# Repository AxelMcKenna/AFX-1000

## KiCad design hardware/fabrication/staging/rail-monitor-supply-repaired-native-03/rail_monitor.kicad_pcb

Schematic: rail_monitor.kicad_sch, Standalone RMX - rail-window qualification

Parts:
C1, C2, C3, C4, C5, C6, C7, C8, C9, C10, C11, C12, C13, C14, C15, C16, C17, C18, C19, C20, C21, C22, C23, C24, C25, C26, C27, C28, C29, C30, C31, C32, C33, C34, C35, C36: 100pF C0G 5%; C_0805_2012Metric
C37, C38, C39, C40, C41, C42, C43, C44, C45, C46, C47, C48: 100nF 16V X7R; C_0805_2012Metric
C49: 2.2uF 16V X7R; C_0805_2012Metric
C50: 10uF 16V X7R; C_0805_2012Metric
C51: 1uF 16V X7R; C_0805_2012Metric
J1, J3: Conn_01x03; PinHeader_1x03_P2.54mm_Vertical
J2: Conn_01x06; PinHeader_1x06_P2.54mm_Vertical
J4: Conn_01x02; PinHeader_1x02_P2.54mm_Vertical
R1, R7, R25, R31: 91k 0.01% 5ppm; R_0805_2012Metric
R2, R4, R8, R10, R11, R14, R16, R19, R21, R22, R26, R28, R32, R33, R35, R36, R39, R41, R44, R45, R47, R48, R51, R53, R56, R58, R59, R62, R64, R67, R69, R70, R73, R75, R77, R80, R82, R84, R85, R88, R90, R92, R96, R98, R99, R103, R105, R106, R108, R111: 10k 0.01% 5ppm; R_0805_2012Metric
R3: 3.57k 0.01% 5ppm; R_0805_2012Metric
R5, R12, R17, R23, R29, R37, R42, R49, R54, R60, R65, R71, R78, R86, R93, R100: 20M 1%; R_0805_2012Metric
R6, R13, R18, R24, R30, R38, R43, R50, R55, R61, R66, R72, R79, R87, R94, R101, R113: 10k 1%; R_0805_2012Metric
R9: 3.01k 0.01% 5ppm; R_0805_2012Metric
R15: 3.4k 0.01% 5ppm; R_0805_2012Metric
R20: 2.87k 0.01% 5ppm; R_0805_2012Metric
R27, R95: 11.5k 0.01% 5ppm; R_0805_2012Metric
R34: 604 0.01% 5ppm; R_0805_2012Metric
R40: 11.3k 0.01% 5ppm; R_0805_2012Metric
R46: 412 0.01% 5ppm; R_0805_2012Metric
R52, R63: 8.2k 0.01% 5ppm; R_0805_2012Metric
R57, R68: 1.78k 0.01% 5ppm; R_0805_2012Metric
R74, R81, R89: 499 0.01% 5ppm; R_0805_2012Metric
R76: 374 0.01% 5ppm; R_0805_2012Metric
R83: 127 0.01% 5ppm; Bourns_CRT0805
R91: 768 0.01% 5ppm; R_0805_2012Metric
R97: 270 0.01% 5ppm; R_0805_2012Metric
R102, R104: 100k 0.01% 5ppm; R_0805_2012Metric
R107, R109: 80.6k 0.01% 5ppm; R_0805_2012Metric
R110: 105k 0.01% 5ppm; R_0805_2012Metric
R112: 100k 1%; R_0805_2012Metric
R114: 330k 1%; R_0805_2012Metric
U1, U2, U3, U4: TLV1824IDR; SOIC-14_3.9x8.7mm_P1.27mm
U5: OPA4192ID; SOIC-14_3.9x8.7mm_P1.27mm
U6: REF5025EIDR; SOIC-8_3.9x4.9mm_P1.27mm
U7: TPS3808G01DBVR; SOT-23-6
U8: TPS3808G33DBVR; SOT-23-6
U9, U10, U11, U12: SN74LVC08APWR; TSSOP-14_4.4x5mm_P0.65mm

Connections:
/5V_DIG: J1.1, R88.1, R95.1
/5V_DIG_OV_OK: R100.1, R101.2, U4.13 (4_OUT), U10.13 (B)
/5V_DIG_OV_REF: C32.1, R99.2, R100.2, U4.11 (4+)
/5V_DIG_OV_REF_BASE: R97.2, R98.1, R99.1
/5V_DIG_OV_SENSE: C31.1, R95.2, R96.1, U4.10 (4-)
/5V_DIG_UV_OK: R93.1, R94.2, U4.14 (3_OUT), U10.12 (A)
/5V_DIG_UV_REF: C30.1, R91.2, R92.1, U4.8 (3-)
/5V_DIG_UV_RT_MID: R88.2, R89.1
/5V_DIG_UV_SENSE: C29.1, R89.2, R90.1, R93.2, U4.9 (3+)
/5V_DIG_WINDOW_OK: U10.11 (Y), U11.13 (B)
/AGND: C1.2, C2.2, C3.2, C4.2, C5.2, C6.2, C7.2, C8.2, C9.2, C10.2, C11.2, C12.2, C13.2, C14.2, C15.2, C16.2, C17.2, C18.2, C19.2, C20.2, C21.2, C22.2, C23.2, C24.2, C25.2, C26.2, C27.2, C28.2, C29.2, C30.2, C31.2, C32.2, C37.2, C38.2, C39.2, C40.2, C41.2, C42.2, C43.2, C44.2, C45.2, C46.2, C47.2, C48.2, C49.2, C50.2, C51.2, J1.3, J2.2, J3.1, J4.1, R2.2, R4.2, R8.2, R10.2, R16.2, R21.2, R26.2, R28.2, R32.2, R35.2, R41.2, R47.2, R53.2, R58.2, R64.2, R69.2, R75.2, R77.2, R82.2, R84.2, R90.2, R92.2, R96.2, R98.2, R111.2, R114.2, U1.12 (V-), U2.12 (V-), U3.12 (V-), U4.12 (V-), U5.3 (N19+), U5.5 (N12+), U5.10 (NBIAS_L+), U5.11 (V-), U5.12 (NBIAS_R+), U6.4 (GND), U7.2 (GND), U8.2 (GND), U9.7 (GND), U10.7 (GND), U11.7 (GND), U12.7 (GND)
/ANALOG_WINDOWS_OK: U12.3 (Y), U12.9 (A)
/BIAS_OK: U11.8 (Y), U12.4 (A)
/FIVES_OK: U11.11 (Y), U12.5 (B)
/HV_OK: U11.3 (Y), U12.1 (A)
/LOCAL_RAIL_OK: R113.2, U7.1 (RESET_N), U8.1 (RESET_N), U12.13 (B)
/LOWV_WINDOWS_OK: U12.6 (Y), U12.10 (B)
/LV_OK: U11.6 (Y), U12.2 (B)
/N12: J2.5, R104.1
/N12_FB: C34.2, R104.2, R105.2, U5.6 (N12-)
/N12_INV: C34.1, R39.1, R44.1, R105.1, U5.7 (N12_OUT)
/N12_OV_OK: R49.1, R50.2, U2.13 (4_OUT), U9.13 (B)
/N12_OV_REF: C16.1, R48.2, R49.2, U2.11 (4+)
/N12_OV_REF_BASE: R46.2, R47.1, R48.1
/N12_OV_REF_MID: R45.2, R46.1
/N12_OV_SENSE: C15.1, R44.2, U2.10 (4-)
/N12_UV_OK: R42.1, R43.2, U2.14 (3_OUT), U9.12 (A)
/N12_UV_REF: C14.1, R40.2, R41.1, U2.8 (3-)
/N12_UV_SENSE: C13.1, R39.2, R42.2, U2.9 (3+)
/N12_WINDOW_OK: U9.11 (Y), U11.5 (B)
/N19: J2.3, R102.1
/N19_FB: C33.2, R102.2, R103.2, U5.2 (N19-)
/N19_INV: C33.1, R14.1, R19.1, R103.1, U5.1 (N19_OUT)
/N19_OV_OK: R23.1, R24.2, U1.13 (4_OUT), U9.5 (B)
/N19_OV_REF: C8.1, R22.2, R23.2, U1.11 (4+)
/N19_OV_REF_BASE: R20.2, R21.1, R22.1
/N19_OV_SENSE: C7.1, R19.2, U1.10 (4-)
/N19_UV_OK: R17.1, R18.2, U1.14 (3_OUT), U9.4 (A)
/N19_UV_REF: C6.1, R15.2, R16.1, U1.8 (3-)
/N19_UV_SENSE: C5.1, R14.2, R17.2, U1.9 (3+)
/N19_WINDOW_OK: U9.6 (Y), U11.2 (B)
/NBIAS_L: J3.2, R106.1
/NBIAS_L_FB: C35.2, R106.2, R107.2, U5.9 (NBIAS_L-)
/NBIAS_L_INV: C35.1, R51.1, R56.1, R107.1, U5.8 (NBIAS_L_OUT)
/NBIAS_L_OV_OK: R60.1, R61.2, U3.1 (2_OUT), U10.2 (B)
/NBIAS_L_OV_REF: C20.1, R59.2, R60.2, U3.7 (2+)
/NBIAS_L_OV_REF_BASE: R57.2, R58.1, R59.1
/NBIAS_L_OV_SENSE: C19.1, R56.2, U3.6 (2-)
/NBIAS_L_UV_OK: R54.1, R55.2, U3.2 (1_OUT), U10.1 (A)
/NBIAS_L_UV_REF: C18.1, R52.2, R53.1, U3.4 (1-)
/NBIAS_L_UV_SENSE: C17.1, R51.2, R54.2, U3.5 (1+)
/NBIAS_L_WINDOW_OK: U10.3 (Y), U11.9 (A)
/NBIAS_R: J3.3, R108.1
/NBIAS_R_FB: C36.2, R108.2, R109.2, U5.13 (NBIAS_R-)
/NBIAS_R_INV: C36.1, R62.1, R67.1, R109.1, U5.14 (NBIAS_R_OUT)
/NBIAS_R_OV_OK: R71.1, R72.2, U3.13 (4_OUT), U10.5 (B)
/NBIAS_R_OV_REF: C24.1, R70.2, R71.2, U3.11 (4+)
/NBIAS_R_OV_REF_BASE: R68.2, R69.1, R70.1
/NBIAS_R_OV_SENSE: C23.1, R67.2, U3.10 (4-)
/NBIAS_R_UV_OK: R65.1, R66.2, U3.14 (3_OUT), U10.4 (A)
/NBIAS_R_UV_REF: C22.1, R63.2, R64.1, U3.8 (3-)
/NBIAS_R_UV_SENSE: C21.1, R62.2, R65.2, U3.9 (3+)
/NBIAS_R_WINDOW_OK: U10.6 (Y), U11.10 (B)
/P12: J2.4, R25.1, R31.1
/P12_OV_OK: R37.1, R38.2, U2.1 (2_OUT), U9.10 (B)
/P12_OV_REF: C12.1, R36.2, R37.2, U2.7 (2+)
/P12_OV_REF_BASE: R34.2, R35.1, R36.1
/P12_OV_REF_MID: R33.2, R34.1
/P12_OV_SENSE: C11.1, R31.2, R32.1, U2.6 (2-)
/P12_UV_OK: R29.1, R30.2, U2.2 (1_OUT), U9.9 (A)
/P12_UV_REF: C10.1, R27.2, R28.1, U2.4 (1-)
/P12_UV_SENSE: C9.1, R25.2, R26.1, R29.2, U2.5 (1+)
/P12_WINDOW_OK: U9.8 (Y), U11.4 (A)
/P19: J2.1, R1.1, R7.1
/P19_OV_OK: R12.1, R13.2, U1.1 (2_OUT), U9.2 (B)
/P19_OV_REF: C4.1, R11.2, R12.2, U1.7 (2+)
/P19_OV_REF_BASE: R9.2, R10.1, R11.1
/P19_OV_SENSE: C3.1, R7.2, R8.1, U1.6 (2-)
/P19_UV_OK: R5.1, R6.2, U1.2 (1_OUT), U9.1 (A)
/P19_UV_REF: C2.1, R3.2, R4.1, U1.4 (1-)
/P19_UV_SENSE: C1.1, R1.2, R2.1, R5.2, U1.5 (1+)
/P19_WINDOW_OK: U9.3 (Y), U11.1 (A)
/PRE_ANALOG_OK: J4.2, R114.1, U12.11 (Y)
/REF_2V5: C49.1, R3.1, R9.1, R15.1, R20.1, R27.1, R33.1, R40.1, R45.1, R52.1, R57.1, R63.1, R68.1, R76.1, R83.1, R91.1, R97.1, U6.6 (VOUT)
/STARTUP_CT: R112.2, U7.4 (CT)
/V3V3_IO: C43.1, C44.1, C45.1, C46.1, C47.1, C48.1, C51.1, J1.2, R6.1, R13.1, R18.1, R24.1, R30.1, R38.1, R43.1, R50.1, R55.1, R61.1, R66.1, R72.1, R79.1, R87.1, R94.1, R101.1, R112.1, R113.1, U7.3 (MR_N), U7.6 (VDD), U8.3 (MR_N), U8.5 (SENSE), U8.6 (VDD), U9.14 (VCC), U10.14 (VCC), U11.14 (VCC), U12.14 (VCC)
/V5_COARSE_SENSE: R110.2, R111.1, U7.5 (SENSE)
/V5_REG: C37.1, C38.1, C39.1, C40.1, C41.1, C42.1, C50.1, J2.6, R73.1, R80.1, R110.1, U1.3 (V+), U2.3 (V+), U3.3 (V+), U4.3 (V+), U5.4 (V+), U6.1 (EN), U6.2 (VIN)
/V5_REG_OV_OK: R86.1, R87.2, U4.1 (2_OUT), U10.10 (B)
/V5_REG_OV_REF: C28.1, R85.2, R86.2, U4.7 (2+)
/V5_REG_OV_REF_BASE: R83.2, R84.1, R85.1
/V5_REG_OV_RT_MID: R80.2, R81.1
/V5_REG_OV_SENSE: C27.1, R81.2, R82.1, U4.6 (2-)
/V5_REG_UV_OK: R78.1, R79.2, U4.2 (1_OUT), U10.9 (A)
/V5_REG_UV_REF: C26.1, R76.2, R77.1, U4.4 (1-)
/V5_REG_UV_RT_MID: R73.2, R74.1
/V5_REG_UV_SENSE: C25.1, R74.2, R75.1, R78.2, U4.5 (1+)
/V5_REG_WINDOW_OK: U10.8 (Y), U11.12 (A)
/WINDOWS_OK: U12.8 (Y), U12.12 (A)

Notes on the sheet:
E13: eight independent UV/OV windows + coarse5V/3.3V guard. PRE_ANALOG_OK is generated in hardware, independent of MCU firmware.
Monitor only: no power generation, rail disconnect/clamp, transient-fault or fabrication approval. Precision/offset/reference allocations require qualification.
Each open-drain comparator has its own pull-up and hysteresis. Do NOT wire comparator outputs together; use the shown AND tree.
Coarse guard holds qualification low while reference/sense amplifiers start. E09/E11/F02 retain settling and fresh-permit requirements.
Main-rail fault envelope extends to +/-3.2% with a conditional headroom review; normal generation remains +/-1%. Analog5V generation must be tighter than its4.90..5.10V accepted envelope.

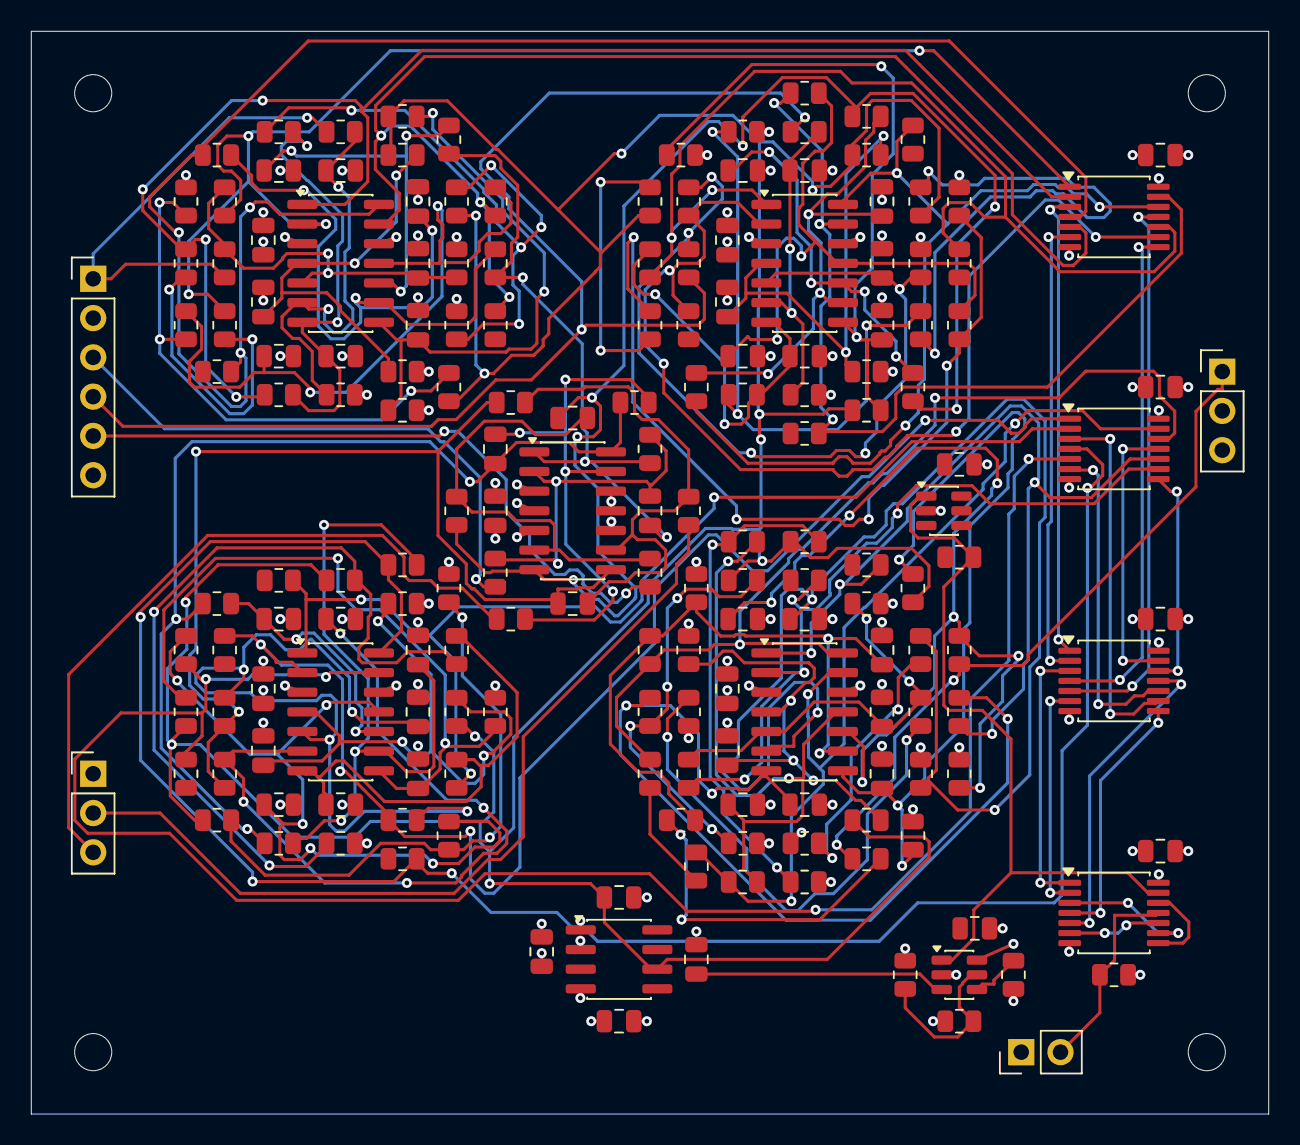
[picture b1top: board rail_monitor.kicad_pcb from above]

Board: 4 copper layers, 80.0 x 70.0 mm, 185 parts (0 on the bottom side), 99 nets.

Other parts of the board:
H1, H2, H3, H4: M2_CLEARANCE; M2_Clearance

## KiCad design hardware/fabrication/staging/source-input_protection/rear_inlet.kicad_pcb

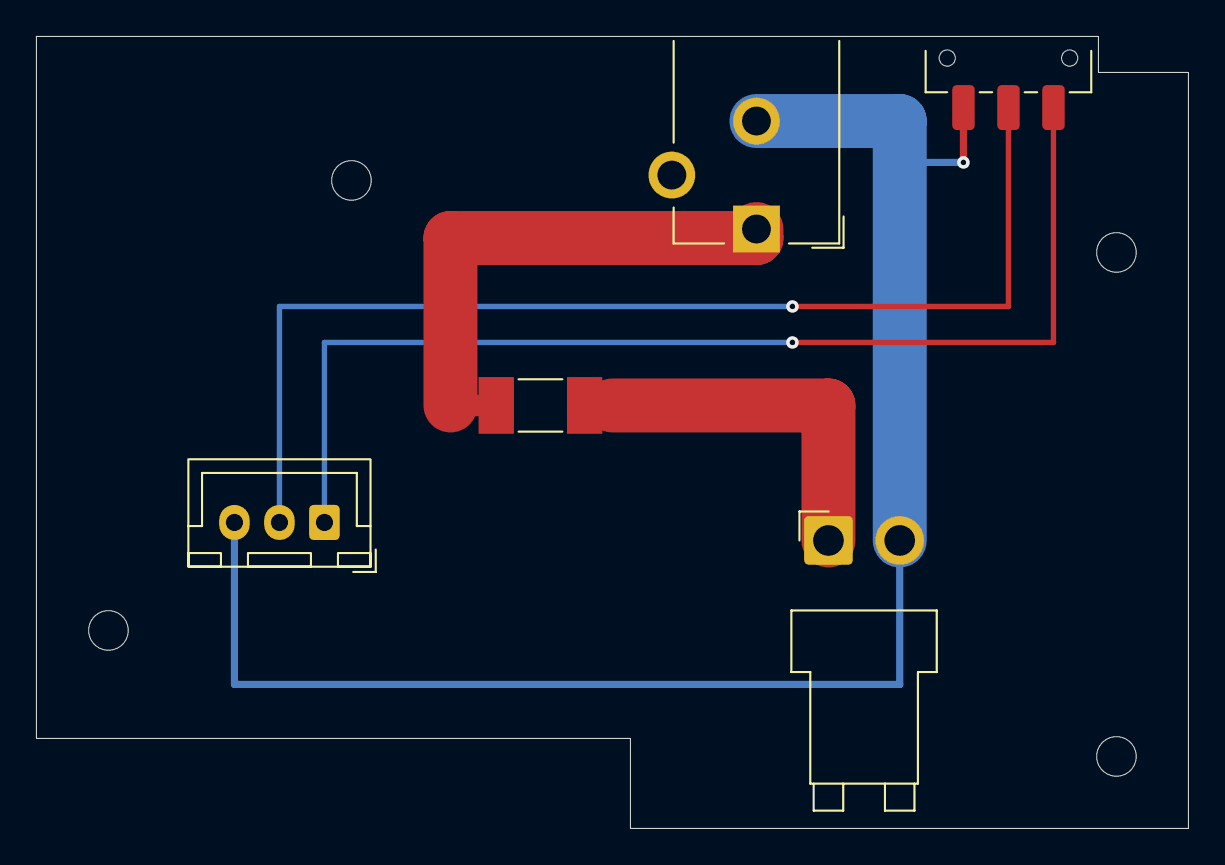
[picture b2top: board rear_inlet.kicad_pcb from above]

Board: 2 copper layers, 64.0 x 44.0 mm, 9 parts (0 on the bottom side), 5 nets.

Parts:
F1: 0451006.MRL 6A 125V; Fuse_Littelfuse-NANO2-451_453
H1, H2, H3, H4: M2_CLEARANCE; MountingHole_2.2mm_M2
J1: PJ-102AH; PJ102AH_RearEdge_E23
J2: B2PS-VH(LF)(SN); JST_VH_B2PS-VH_1x02_P3.96mm_Horizontal
J3: B3B-XH-A(LF)(SN); JST_XH_B3B-XH-A_1x03_P2.50mm_Vertical
S1: JS102011SAQN; JS102011SAQN_RearEdge_E23

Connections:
/AGND: J1.2, J2.2, J3.3, S1.3
/DC_IN: F1.2, J2.1
/DC_JACK: F1.1, J1.1
/POWER_RUN: J3.2, S1.2
/SWITCH_SUPPLY: J3.1, S1.1
